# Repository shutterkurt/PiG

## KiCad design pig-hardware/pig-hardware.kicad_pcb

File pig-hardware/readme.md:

Credits
=======

Silkscreen icons for pig, hat and shutter come from:

<div>
Icons made by <a href="http://www.freepik.com" title="Freepik">Freepik</a> from 
<a href="http://www.flaticon.com" title="Flaticon">www.flaticon.com</a> is licensed by 
<a href="http://creativecommons.org/licenses/by/3.0/" title="Creative Commons BY 3.0">CC BY 3.0</a>
</div>

and then scaled by python script:

http://www.smallbulb.net/kicad_mod-scaler

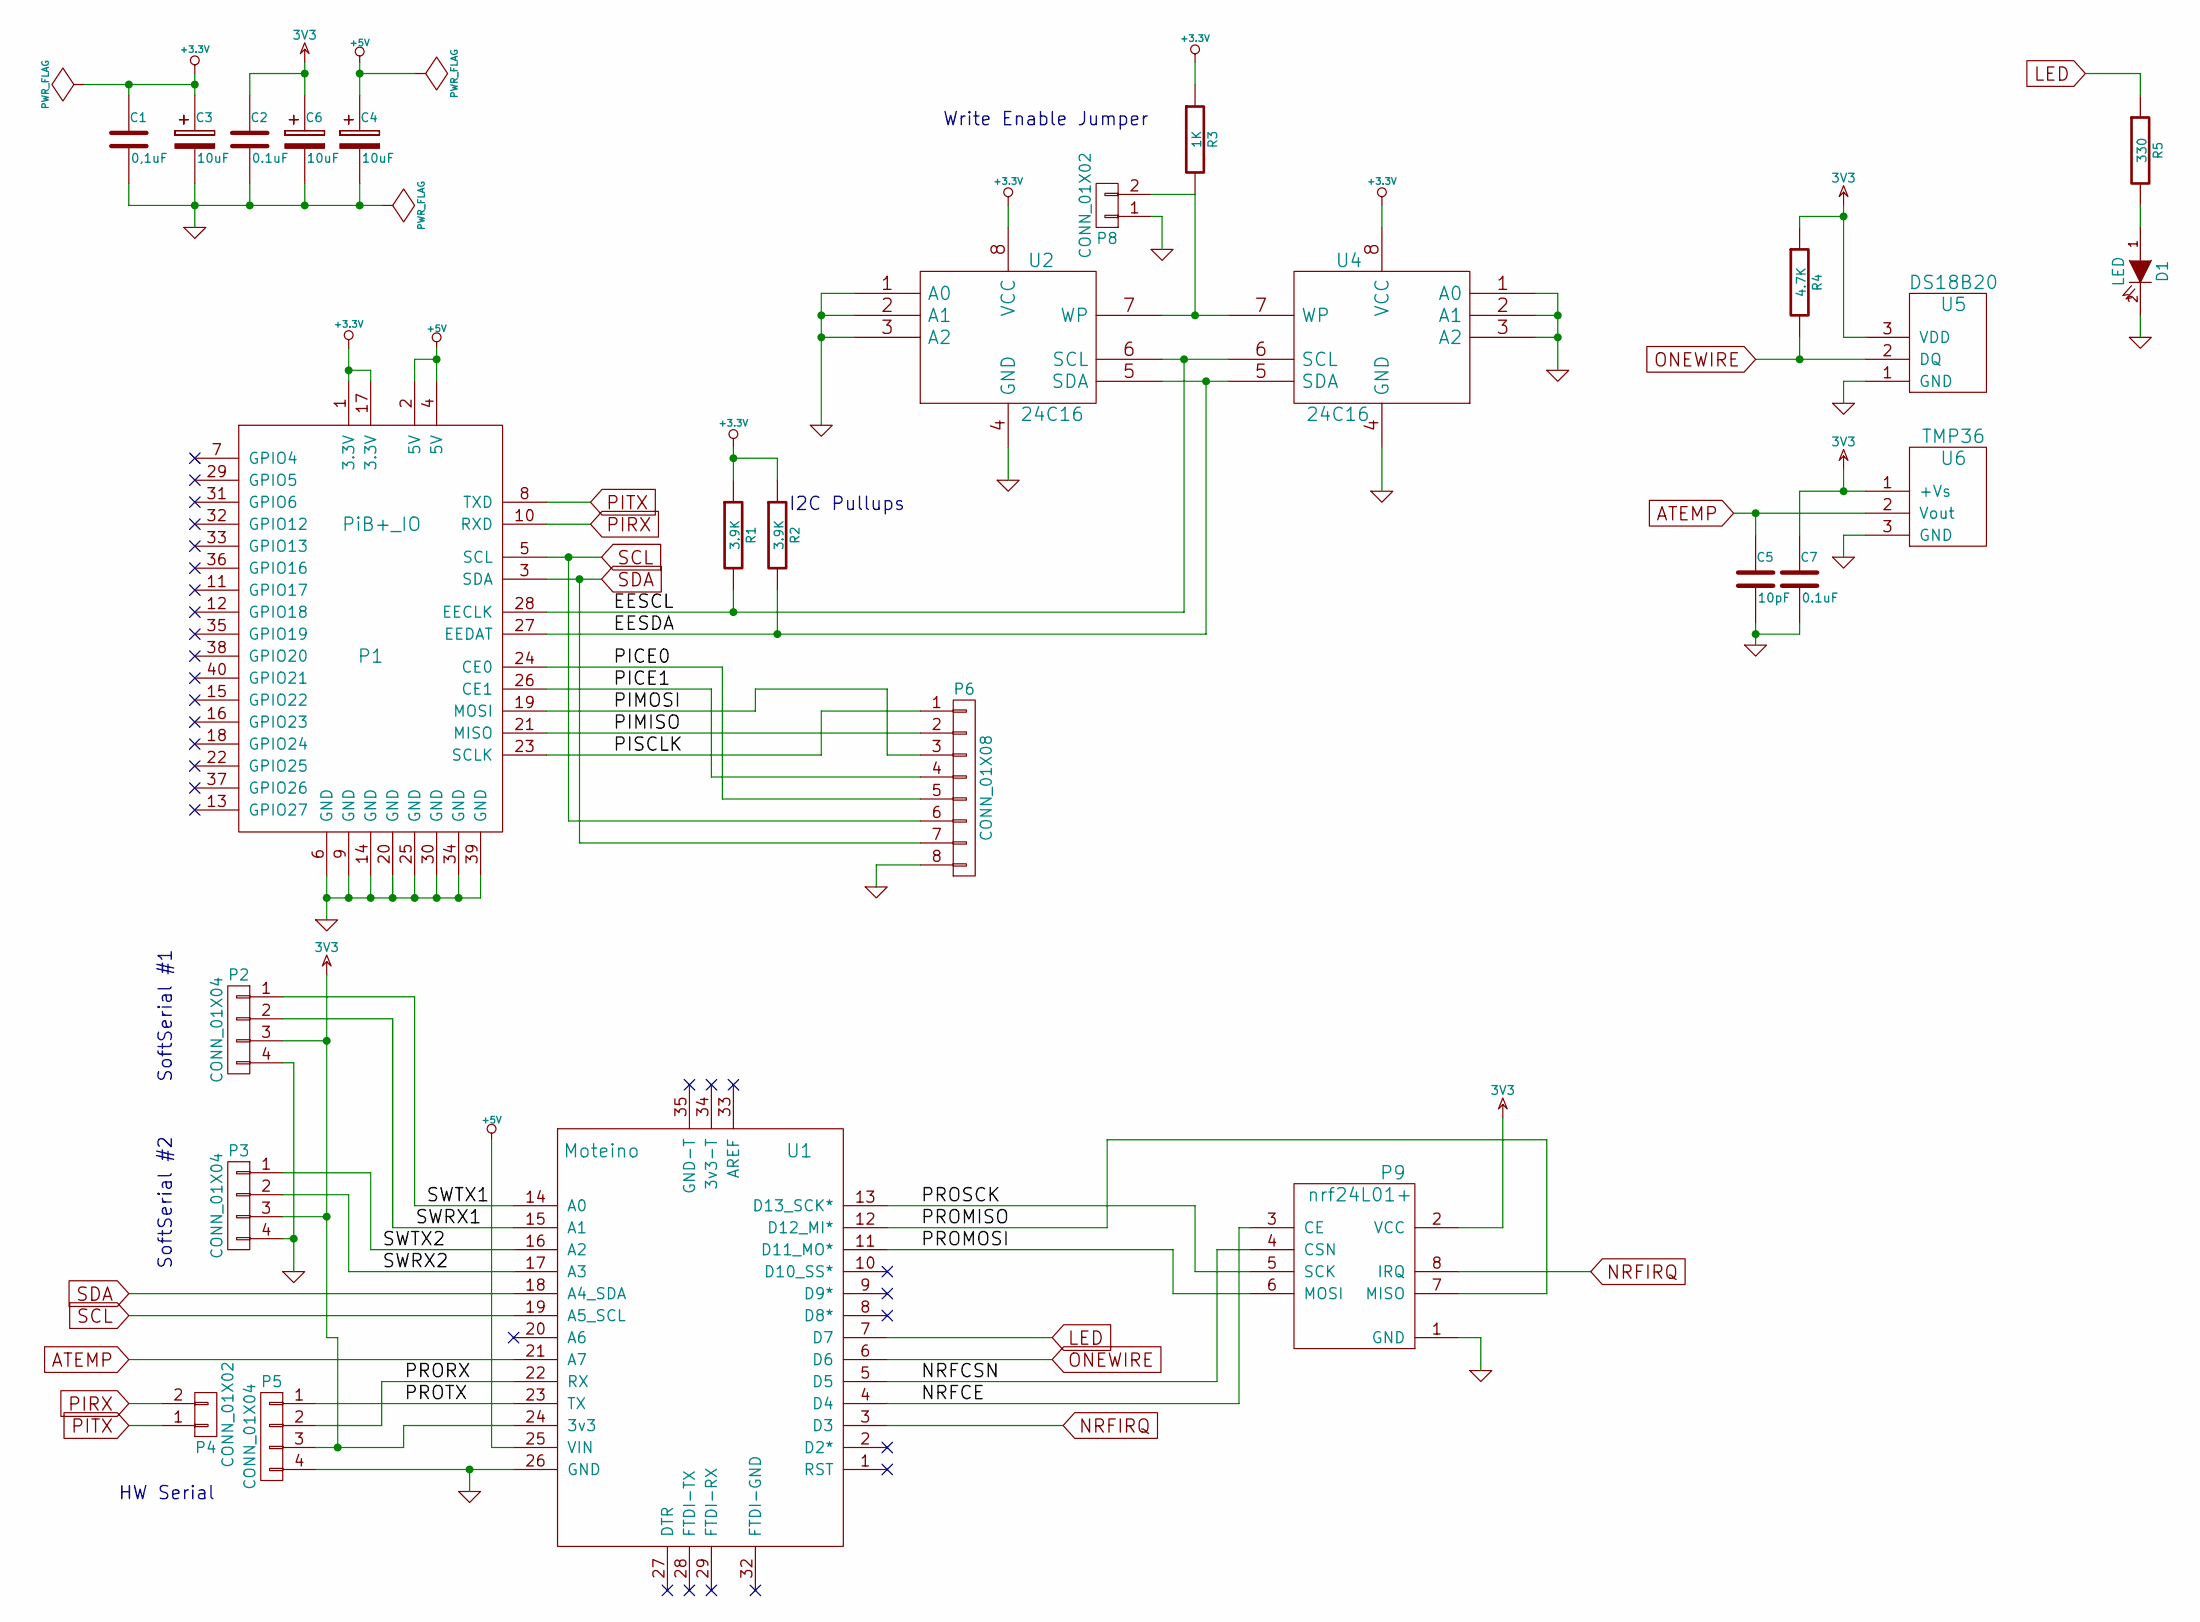
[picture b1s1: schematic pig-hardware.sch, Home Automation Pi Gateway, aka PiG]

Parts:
C1: 0,1uF; C1
C2, C7: 0.1uF; C1
C3, C4, C6: 10uF; C1V5
C5: 10pF; C1
D1: LED; LED-3MM
P1: PiB+_IO; Socket_Strip_Straight_2x20
P2, P3, P5: CONN_01X04; Pin_Header_Straight_1x04
P4, P8: CONN_01X02; Pin_Header_Straight_1x02
P6: CONN_01X08; Pin_Header_Straight_1x08
P9: nrf24L01+; nrf24L01
R1, R2: 3.9K; R1
R3: 1K; R1
R4: 4.7K; R1
R5: 330; R1
U1: Moteino
U2: 24C16; PDIP-8
U4: 24C16; SOIC-8-W
U5: DS18B20; TO-92-Free-inline-narrow-oval
U6: TMP36; TO-92-Free-inline-narrow-oval

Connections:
3V3: C2.1, C6.1, C7.1, P2.3, P3.3, P5.3, P9.2 (VCC), R4.1, U1.24 (3v3), U5.3 (VDD), U6.1 (+Vs)
+3.3V: C1.1, C3.1, P1.1 (3.3V), P1.17 (3.3V), R1.1, R2.1, R3.1, U2.8 (VCC), U4.8 (VCC)
+5V: C4.1, P1.2 (5V), P1.4 (5V), U1.25 (VIN)
/EESCL: P1.28 (EECLK), R1.2, U2.6 (SCL), U4.6 (SCL)
/EESDA: P1.27 (EEDAT), R2.2, U2.5 (SDA), U4.5 (SDA)
/NRFCE: P9.3 (CE), U1.4 (D4)
/NRFCSN: P9.4 (CSN), U1.5 (D5)
/PICE0: P1.24 (CE0), P6.5
/PICE1: P1.26 (CE1), P6.4
/PIMISO: P1.21 (MISO), P6.2
/PIMOSI: P1.19 (MOSI), P6.3
/PISCLK: P1.23 (SCLK), P6.1
/PROMISO: P9.7 (MISO), U1.12 (D12_MI*)
/PROMOSI: P9.6 (MOSI), U1.11 (D11_MO*)
/PRORX: P5.2, U1.22 (RX)
/PROSCK: P9.5 (SCK), U1.13 (D13_SCK*)
/PROTX: P5.1, U1.23 (TX)
/SWRX1: P2.2, U1.15 (A1)
/SWRX2: P3.2, U1.17 (A3)
/SWTX1: P2.1, U1.14 (A0)
/SWTX2: P3.1, U1.16 (A2)
ATEMP: C5.1, U1.21 (A7), U6.2 (Vout)
GND: C1.2, C2.2, C3.2, C4.2, C5.2, C6.2, C7.2, D1.2 (K), P1.6 (GND), P1.9 (GND), P1.14 (GND), P1.20 (GND), P1.25 (GND), P1.30 (GND), P1.34 (GND), P1.39 (GND), P2.4, P3.4, P5.4, P6.8, P8.1, P9.1 (GND), U1.26 (GND), U2.1 (A0), U2.2 (A1), U2.3 (A2), U2.4 (GND), U4.1 (A0), U4.2 (A1), U4.3 (A2), U4.4 (GND), U5.1 (GND), U6.3 (GND)
LED: R5.1, U1.7 (D7)
NRFIRQ: P9.8 (IRQ), U1.3 (D3)
unnamed: D1.1 (A), R5.2
unnamed: P8.2, R3.2, U2.7 (WP), U4.7 (WP)
ONEWIRE: R4.2, U1.6 (D6), U5.2 (DQ)
PIRX: P1.10 (RXD), P4.2
PITX: P1.8 (TXD), P4.1
SCL: P1.5 (SCL), P6.6, U1.19 (A5_SCL)
SDA: P1.3 (SDA), P6.7, U1.18 (A4_SDA)

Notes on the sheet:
Write Enable Jumper
HW Serial
SoftSerial #1
SoftSerial #2
I2C Pullups

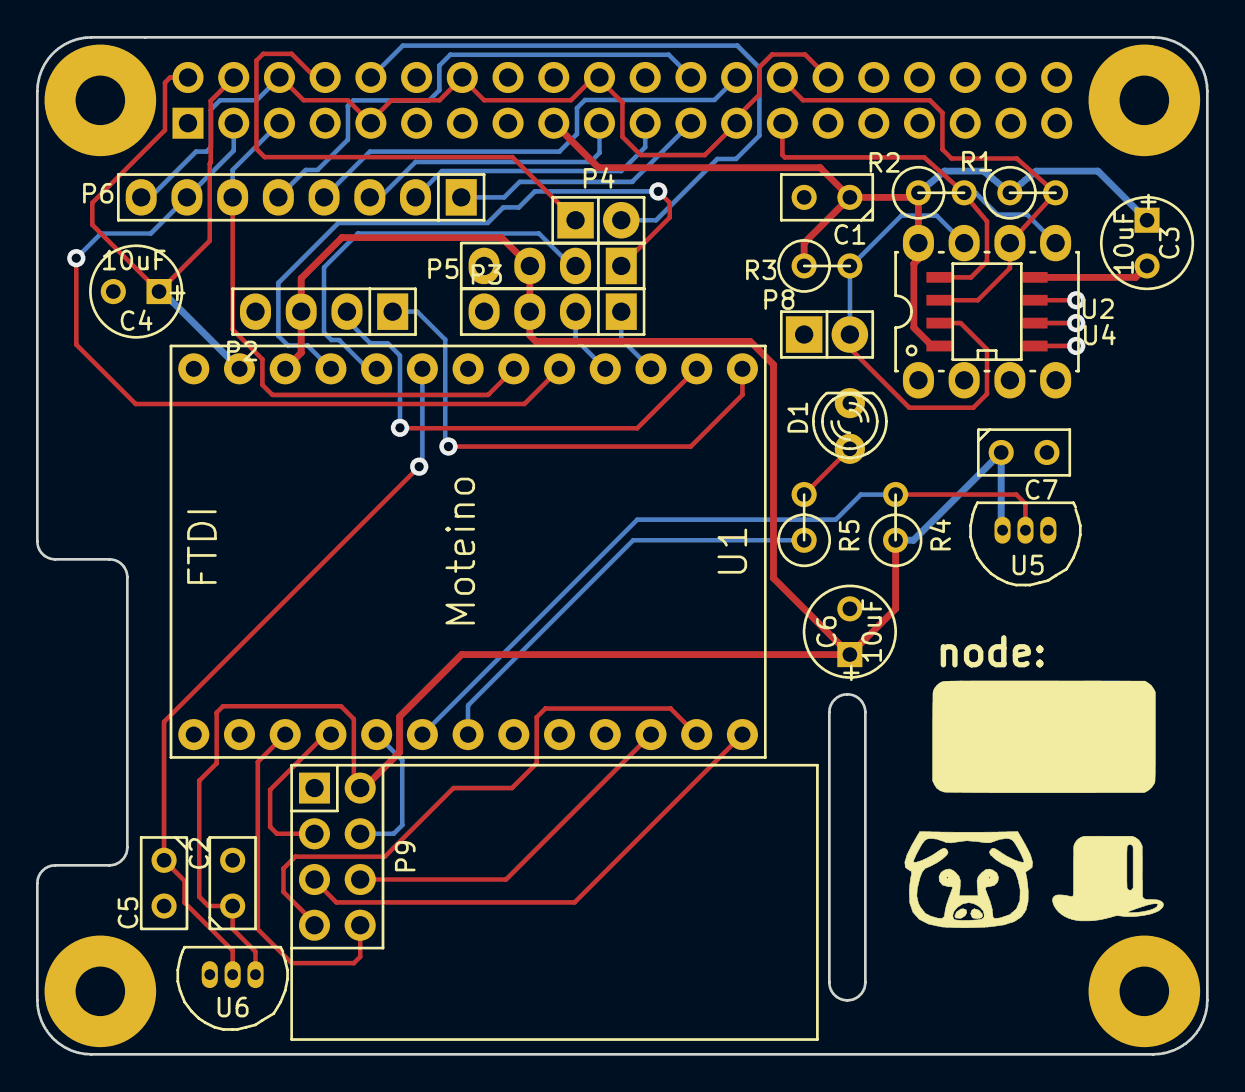
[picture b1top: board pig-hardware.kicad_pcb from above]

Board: 2 copper layers, 65.0 x 56.5 mm, 30 parts (1 on the bottom side), 32 nets.

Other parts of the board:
MechanicalHole-2m5, MechanicalHole-2m5#2, MechanicalHole-2m5#3, MechanicalHole-2m5#4: VAL**; MechanicalHole-2m5

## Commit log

2015-02-15 some more work in progress
2015-02-18 swapped pro with moteino
2015-02-22 removed pro & rfm from pcb
2015-02-23 update pcb for moteino
2015-04-12 final as fabbed
2015-04-13 final gerbers
